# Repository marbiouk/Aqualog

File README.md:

Aqualog
=======

Arduino based aquarium logger

Sensor package
1 x pH
2 x salinity sensor
2 x temp in water
1 x room temp
1 x room humidity (528-3171)
1 x pressure sensor (tank level)

Sundries
1 x 20x2 or 16x2 LCD display
1 x wireless connection probably xbee

Power regulation
12v in
3.3
5v

Connectors
3 x 2 pin Molex crimp (temp)
2 pin power 

Notes
Mount pressure sensor in housing direct to board.

Base unit -uploader

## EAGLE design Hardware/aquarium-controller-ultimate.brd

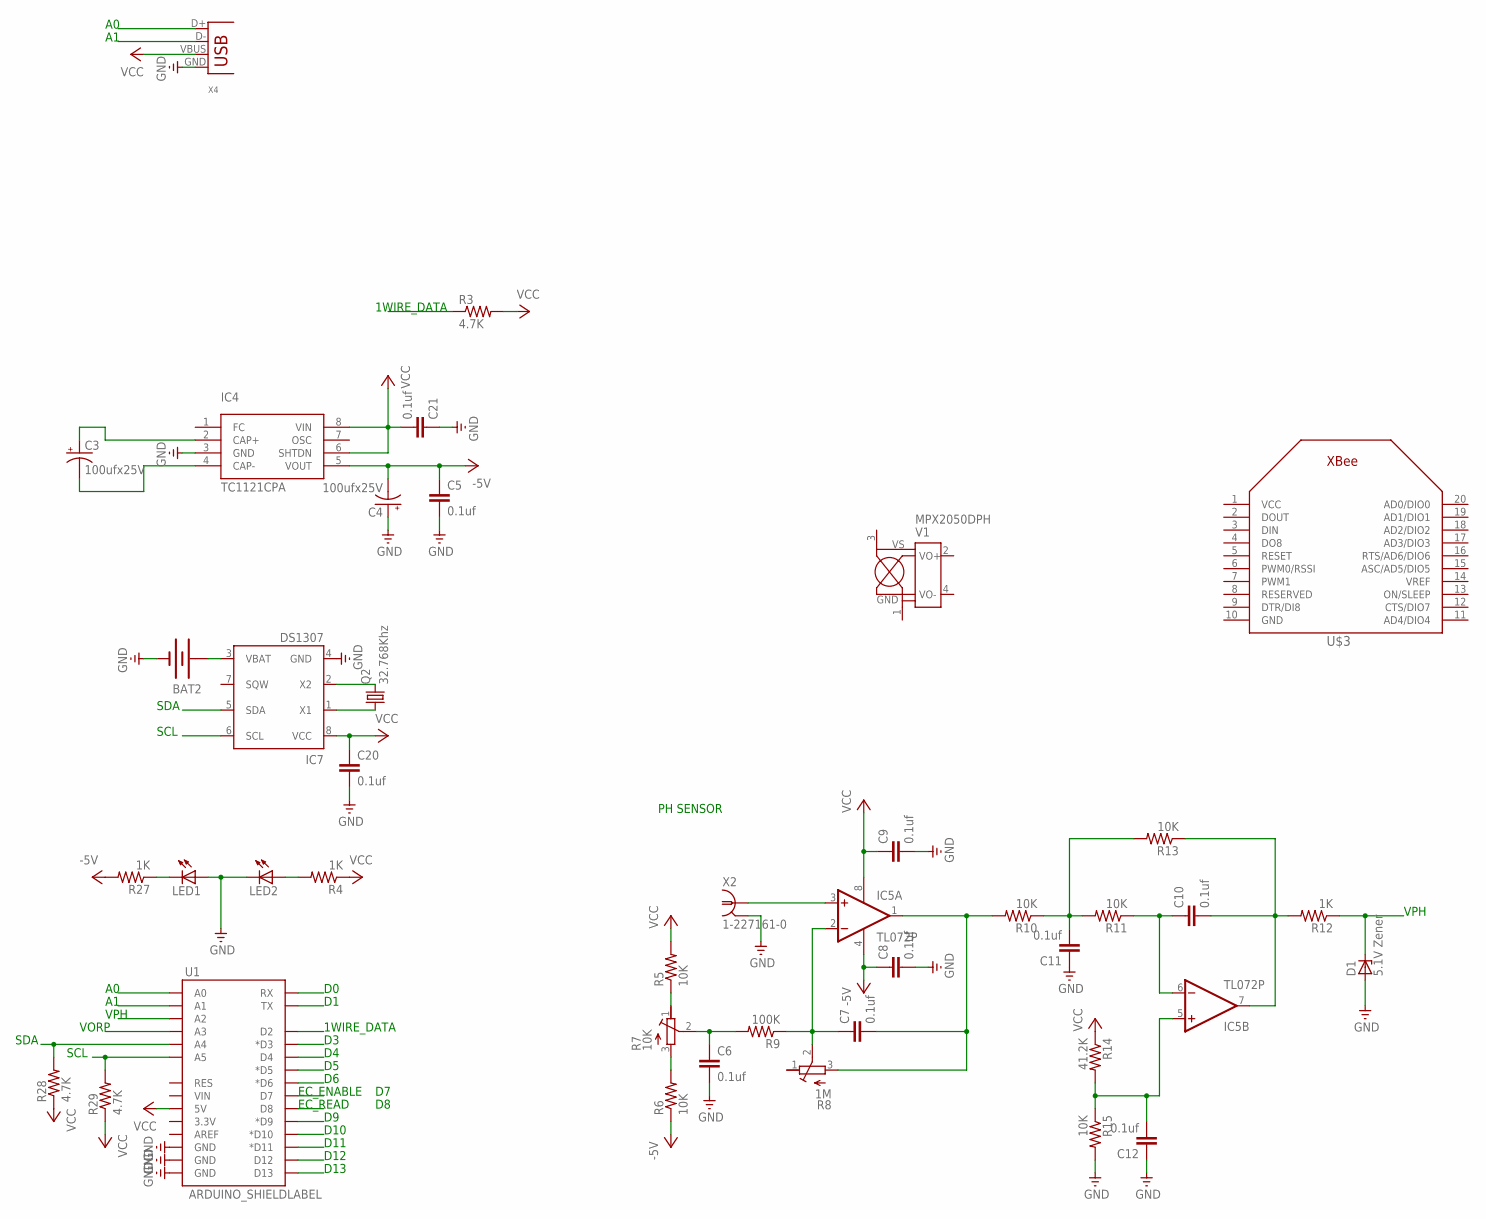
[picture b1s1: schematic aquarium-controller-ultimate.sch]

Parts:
BAT2: BATTERY20PTH; BATTCOM_20MM_PTH
C3, C4: 100ufx25V; E2,5-7
C5, C6, C7, C8, C9, C10, C11, C12, C20, C21: 0.1uf; C025-025X050
D1: 5.1V Zener; DO35Z10
IC4: TC1121CPA; DIL8
IC5: TL072P; DIL08
IC7: DS1307; DIL08
LED1, LED2: LED3MM
Q2: 32.768Khz; TC38H
R3, R28, R29: 4.7K; 0207/10
R4, R12, R27: 1K; 0207/10
R5, R6, R10, R11, R13, R15: 10K; 0207/10
R7: 10K; RTRIM43P
R8: 1M; RTRIM43P
R9: 100K; 0207/10
R14: 41.2K; 0207/10
U1: ARDUINO_SHIELDLABEL; DUEMILANOVE_SHIELD
U$3: XBEE
V1: MPX2050DPH
X2: 1-227161-0; AMP_227161
X4: USB-A-H

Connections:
1WIRE_DATA: R3.1, U1.D2
-5V: C4.-, C5.1, C8.1, IC4.5 (VOUT), IC5.4 (V-), R6.1, R27.2
A0: U1.A0, X4.D+
A1: U1.A1, X4.D-
D0: U1.RX
D1: U1.TX
D3: U1.D3 (*D3)
D4: U1.D4
D5: U1.D5 (*D5)
D6: U1.D6 (*D6)
D9: U1.D9 (*D9)
D10: U1.D10 (*D10)
D11: U1.D11 (*D11)
D12: U1.D12
D13: U1.D13
ENABLE: U1.D7
GND: BAT2.2 (-), C4.+, C5.2, C6.2, C8.2, C9.2, C11.1, C12.1, C20.2, C21.1, D1.A, IC4.3 (GND), IC7.4 (GND), LED1.A, LED2.K (C), R15.2, U1.GND@0 (GND), U1.GND@1 (GND), U1.GND@2 (GND), X2.2 (GND), X4.GND
unnamed: LED2.A, R4.2
unnamed: LED1.K (C), R27.1
unnamed: C3.+, IC4.2 (CAP+)
unnamed: C3.-, IC4.4 (CAP-)
unnamed: R6.2, R7.3 (E)
unnamed: R5.1, R7.1 (A)
unnamed: C6.1, R7.2 (S), R9.2
unnamed: C7.1, IC5.2 (-IN), R8.2 (S), R9.1
unnamed: C7.2, IC5.1 (OUT), R8.3 (E), R10.2
unnamed: IC5.3 (+IN), X2.1
unnamed: C11.2, R10.1, R11.2, R13.2
unnamed: C10.1, IC5.6 (-IN), R11.1
unnamed: C10.2, IC5.7 (OUT), R12.2, R13.1
unnamed: C12.2, IC5.5 (+IN), R14.2, R15.1
unnamed: IC7.2 (X2), Q2.2
unnamed: IC7.1 (X1), Q2.1
unnamed: BAT2.1 (+), IC7.3 (VBAT)
PROBE_2: U1.D8
SCL: IC7.6 (SCL), R29.2, U1.A5
SDA: IC7.5 (SDA), R28.2, U1.A4
VCC: C9.1, C20.1, C21.2, IC4.6 (SHTDN), IC4.8 (VIN), IC5.8 (V+), IC7.8 (VCC), R3.2, R4.1, R5.2, R14.1, R28.1, R29.1, U1.5V, X4.VBUS
VORP: U1.A3
VPH: D1.C, R12.1, U1.A2

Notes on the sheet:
VPH
SDA
SCL
1WIRE_DATA
D10
D11
D12
D13
VORP
EC_ENABLE
EC_READ
PH SENSOR

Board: 2 copper layers, 42 parts (1 on the bottom side), 26 nets, no tracks yet.

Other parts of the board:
U$2: OSHW1

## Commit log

2012-09-23 Uploaded files
